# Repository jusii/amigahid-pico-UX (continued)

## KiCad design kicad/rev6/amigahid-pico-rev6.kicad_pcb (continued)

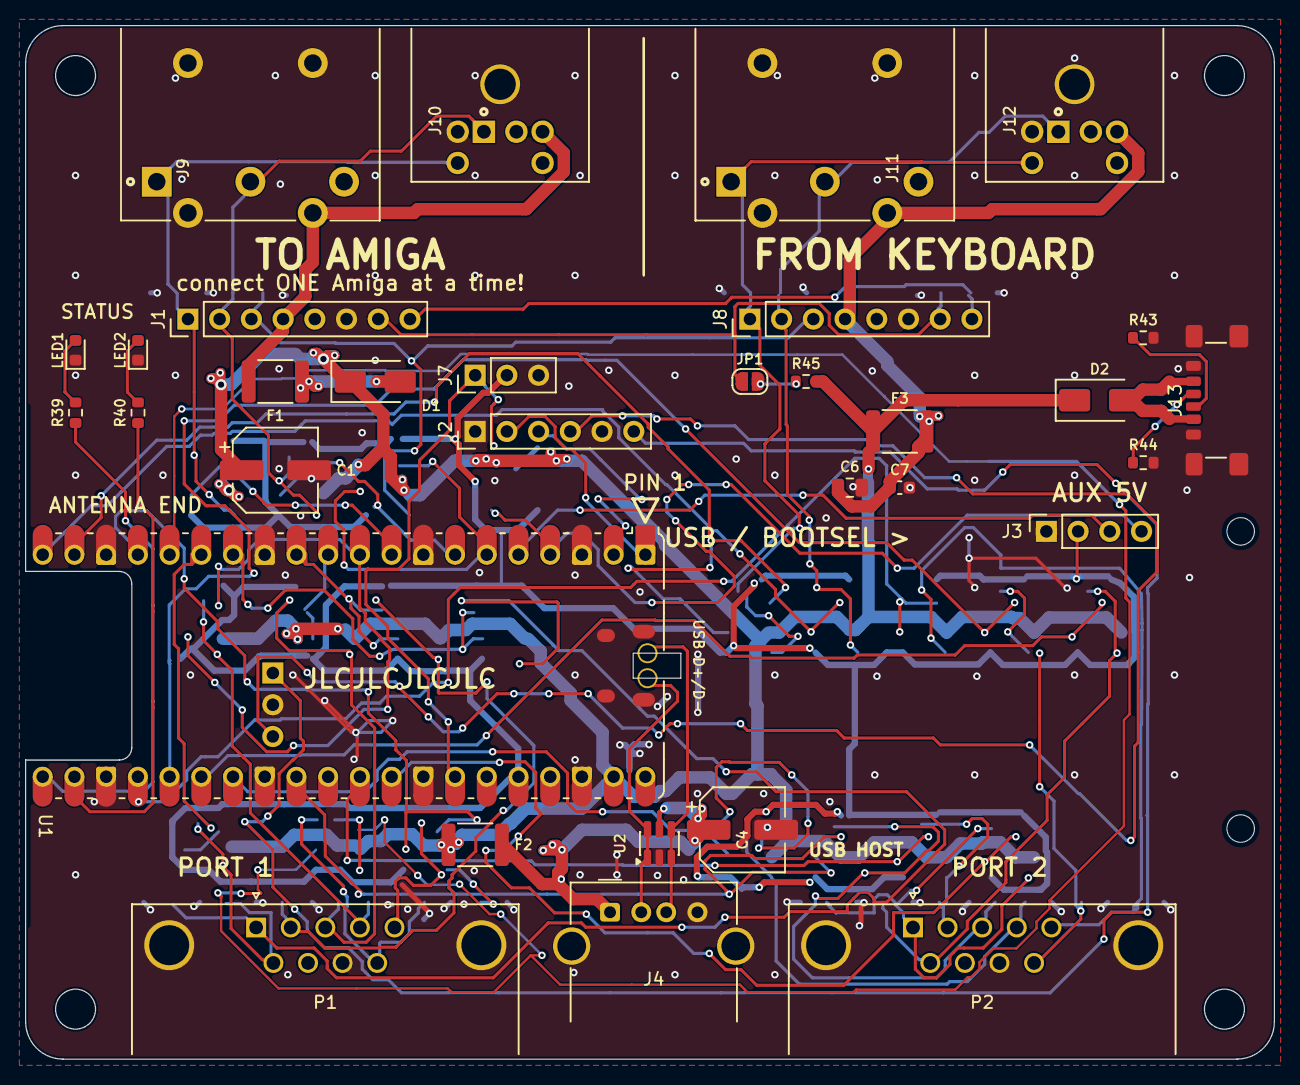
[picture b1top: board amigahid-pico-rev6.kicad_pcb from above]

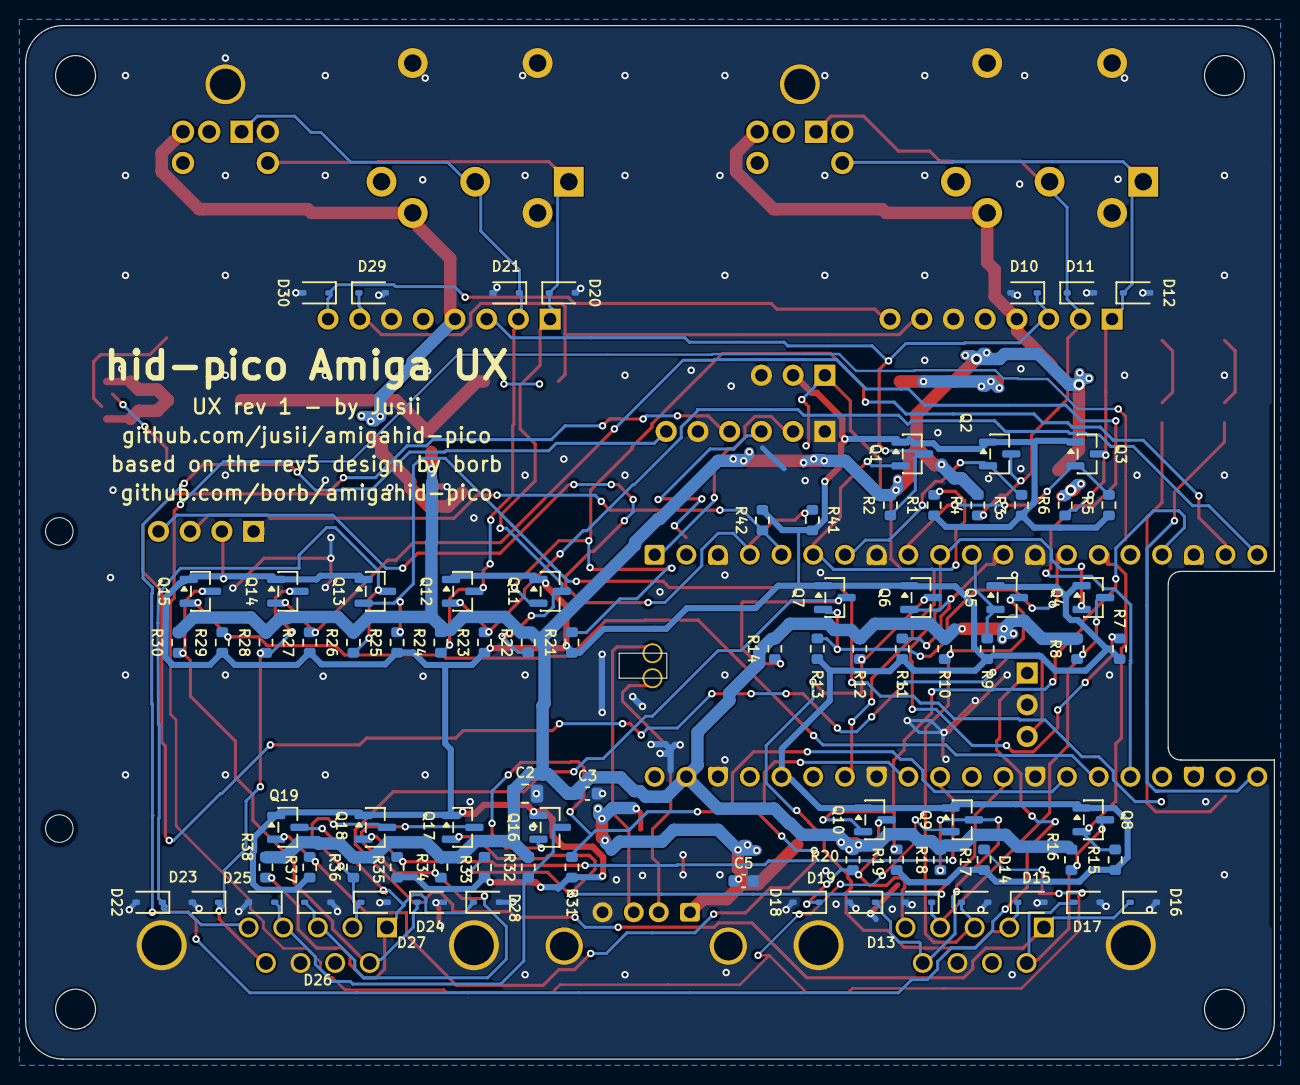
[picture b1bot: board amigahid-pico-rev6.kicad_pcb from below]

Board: 2 copper layers, 100.0 x 82.8 mm, 117 parts (83 on the bottom side), 64 nets.

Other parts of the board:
H1, H2: M2 OLED post; MountingHole_2.2mm_M2

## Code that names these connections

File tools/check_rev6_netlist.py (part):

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        rep.chk("E.led_passthrough",
                nl.net_of("J1", "7") == nl.net_of("J8", "7") == "kb_pwrled"
                and nl.net_of("J1", "8") == nl.net_of("J8", "8") == "kb_drvled",
                "J1/J8 pins 7 and 8 must pair up on kb_pwrled / kb_drvled")


def check_power(rep, nl, low_nets):
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        mid1 = None
    else:
        nets = two_pin_nets("F1")
        rep.chk("F.F1", "amiga_5v" in nets and len(nets) == 2,
                "F1 must bridge AMIGA_5V and the D1 anode node, found %s" % sorted(nets))
        mid1 = next(iter(nets - {"amiga_5v"}), None) if "amiga_5v" in nets else None
        if "polyfuse" not in nl.desc("F1") and "fuse" not in nl.desc("F1"):
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        rep.chk("F.JP1", False, "JP1 (kb_pwrled to SYS5V solder jumper) missing")
    else:
        nets = {nl.net_of("JP1", p) for p in nl.comp_pins.get("JP1", [])}
        rep.chk("F.JP1", "kb_pwrled" in nets and len(nets) == 2,
                "JP1 must bridge kb_pwrled and the SYS5V ballast resistor, found %s"
                % sorted(nl.net_raw.get(n, str(n)) for n in nets))
        mid = next(iter(nets - {"kb_pwrled"}), None) if "kb_pwrled" in nets else None
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    rep.chk("F.gates_on_3v3", len(gates) == 19,
            "expected 19 BSS138 gates on +3V3, found %d" % len(gates))
    lo = [r for r in nl.comps if is_res(nl, r, 10e3) and "3v3" in nl.two_pin_bridge(r)]
    hi = [r for r in nl.comps if is_res(nl, r, 10e3) and "sys5v" in nl.two_pin_bridge(r)]
    rep.chk("F.pullups_3v3", len(lo) == 19,
            "expected 19 low-side 10k pull-ups to +3V3, found %d" % len(lo))
    rep.chk("F.pullups_sys5v", len(hi) == 19,
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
